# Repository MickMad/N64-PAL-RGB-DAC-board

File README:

N64 PAL RGB DAC board

Created by Michele Perla

The tile says it all. The hackaday project page says it even better :)

Inspired by Tim Worthington's PAL RGB mod : http://members.optusnet.com.au/eviltim/n64rgb/n64rgb.html

Hackaday.io project page : https://hackaday.io/project/4098-n64-pal-rgb-dac-board

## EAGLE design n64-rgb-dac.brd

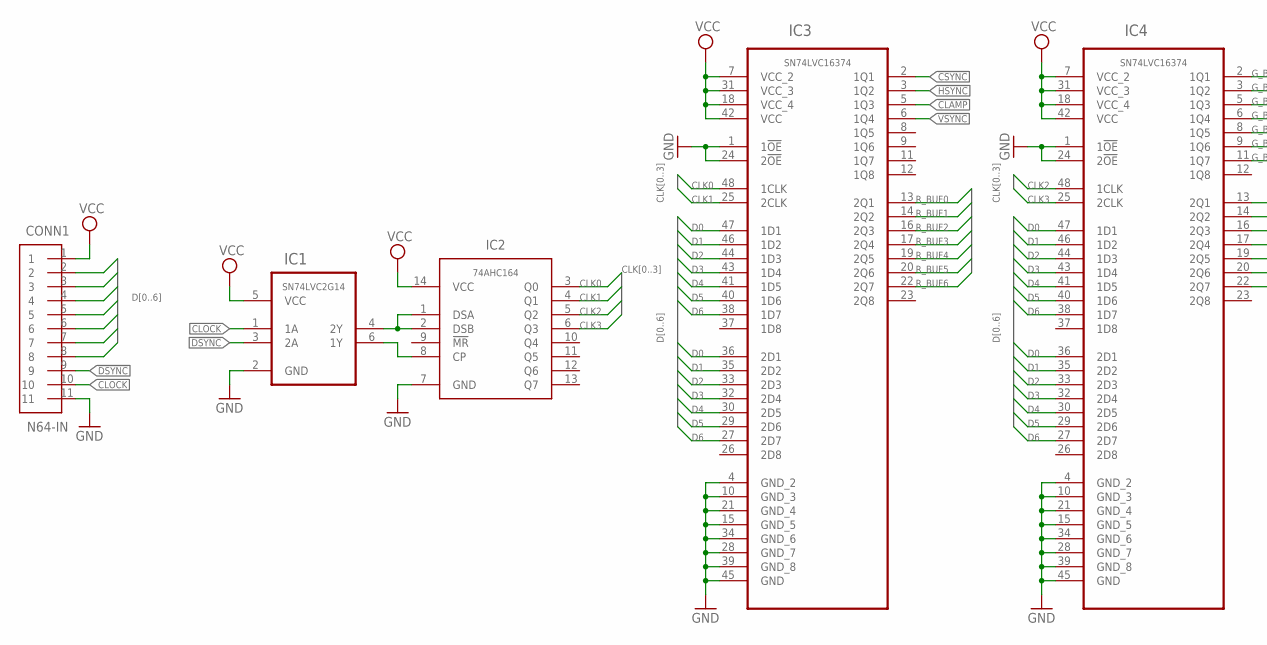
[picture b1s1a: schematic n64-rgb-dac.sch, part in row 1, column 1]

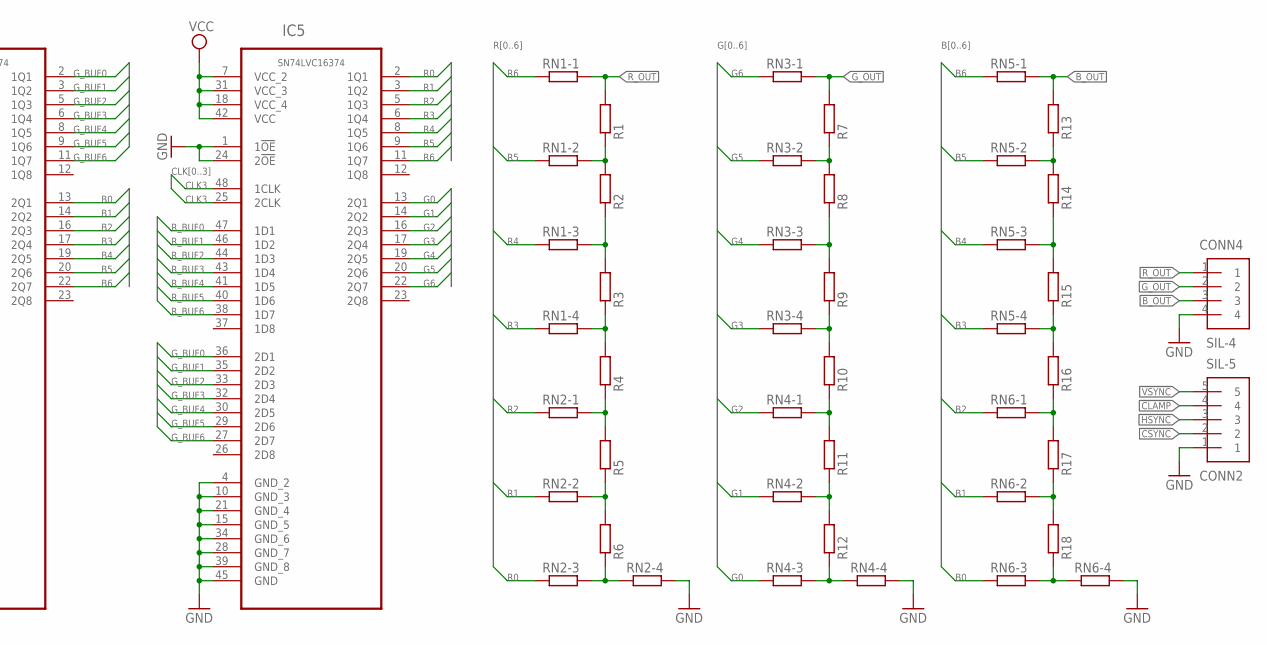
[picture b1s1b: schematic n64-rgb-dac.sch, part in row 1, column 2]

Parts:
CONN1: N64-IN; SIL-SMD-11
CONN2: SIL-5; SIL-SMD-5
CONN4: SIL-4; SIL-SMD-4
IC1: SN74LVC2G14; SOT65P210X110-6N
IC2: 74AHC164PW; SOT402-1
IC3, IC4, IC5: SN74LVC16374DL; SOP63P1035X279-48N
R1, R2, R3, R4, R5, R6, R7, R8, R9, R10, R11, R12, R13, R14, R15, R16, R17, R18: R-EU_R0603; R0603
RN1, RN2, RN3, RN4, RN5, RN6: TC164; R0603_NET_4

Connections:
!CLAMP: CONN2.4, IC3.5 (1Q3)
!CSYNC: CONN2.2, IC3.2 (1Q1)
!DSYNC: CONN1.9, IC1.3 (2A)
!HSYNC: CONN2.3, IC3.3 (1Q2)
!VSYNC: CONN2.5, IC3.6 (1Q4)
B0: IC4.13 (2Q1), RN6.5 (1)
B1: IC4.14 (2Q2), RN6.3 (1)
B2: IC4.16 (2Q3), RN6.1
B3: IC4.17 (2Q4), RN5.7 (1)
B4: IC4.19 (2Q5), RN5.5 (1)
B5: IC4.20 (2Q6), RN5.3 (1)
B6: IC4.22 (2Q7), RN5.1
B_OUT: CONN4.3, R13.2, RN5.2
CLK0: IC2.3 (Q0), IC3.48 (1CLK)
CLK1: IC2.4 (Q1), IC3.25 (2CLK)
CLK2: IC2.5 (Q2), IC4.48 (1CLK)
CLK3: IC2.6 (Q3), IC4.25 (2CLK), IC5.25 (2CLK), IC5.48 (1CLK)
CLOCK: CONN1.10, IC1.1 (1A)
D0: CONN1.2, IC3.36 (2D1), IC3.47 (1D1), IC4.36 (2D1), IC4.47 (1D1)
D1: CONN1.3, IC3.35 (2D2), IC3.46 (1D2), IC4.35 (2D2), IC4.46 (1D2)
D2: CONN1.4, IC3.33 (2D3), IC3.44 (1D3), IC4.33 (2D3), IC4.44 (1D3)
D3: CONN1.5, IC3.32 (2D4), IC3.43 (1D4), IC4.32 (2D4), IC4.43 (1D4)
D4: CONN1.6, IC3.30 (2D5), IC3.41 (1D5), IC4.30 (2D5), IC4.41 (1D5)
D5: CONN1.7, IC3.29 (2D6), IC3.40 (1D6), IC4.29 (2D6), IC4.40 (1D6)
D6: CONN1.8, IC3.27 (2D7), IC3.38 (1D7), IC4.27 (2D7), IC4.38 (1D7)
G0: IC5.13 (2Q1), RN4.5 (1)
G1: IC5.14 (2Q2), RN4.3 (1)
G2: IC5.16 (2Q3), RN4.1
G3: IC5.17 (2Q4), RN3.7 (1)
G4: IC5.19 (2Q5), RN3.5 (1)
G5: IC5.20 (2Q6), RN3.3 (1)
G6: IC5.22 (2Q7), RN3.1
GND: CONN1.11, CONN2.1, CONN4.4, IC1.2 (GND), IC2.7 (GND), IC3.1 (1!OE), IC3.4 (GND_2), IC3.10 (GND_3), IC3.15 (GND_5), IC3.21 (GND_4), IC3.24 (2!OE), IC3.28 (GND_7), IC3.34 (GND_6), IC3.39 (GND_8), IC3.45 (GND), IC4.1 (1!OE), IC4.4 (GND_2), IC4.10 (GND_3), IC4.15 (GND_5), IC4.21 (GND_4), IC4.24 (2!OE), IC4.28 (GND_7), IC4.34 (GND_6), IC4.39 (GND_8), IC4.45 (GND), IC5.1 (1!OE), IC5.4 (GND_2), IC5.10 (GND_3), IC5.15 (GND_5), IC5.21 (GND_4), IC5.24 (2!OE), IC5.28 (GND_7), IC5.34 (GND_6), IC5.39 (GND_8), IC5.45 (GND), RN2.8 (2), RN4.8 (2), RN6.8 (2)
G_BUF0: IC4.2 (1Q1), IC5.36 (2D1)
G_BUF1: IC4.3 (1Q2), IC5.35 (2D2)
G_BUF2: IC4.5 (1Q3), IC5.33 (2D3)
G_BUF3: IC4.6 (1Q4), IC5.32 (2D4)
G_BUF4: IC4.8 (1Q5), IC5.30 (2D5)
G_BUF5: IC4.9 (1Q6), IC5.29 (2D6)
G_BUF6: IC4.11 (1Q7), IC5.27 (2D7)
G_OUT: CONN4.2, R7.2, RN3.2
unnamed: IC1.4 (2Y), IC2.1 (DSA), IC2.2 (DSB)
unnamed: IC1.6 (1Y), IC2.8 (CP)
unnamed: R1.1, R2.2, RN1.4 (2)
unnamed: R2.1, R3.2, RN1.6 (2)
unnamed: R3.1, R4.2, RN1.8 (2)
unnamed: R6.1, RN2.6 (2), RN2.7 (1)
unnamed: R7.1, R8.2, RN3.4 (2)
unnamed: R5.1, R6.2, RN2.4 (2)
unnamed: R4.1, R5.2, RN2.2
unnamed: R8.1, R9.2, RN3.6 (2)
unnamed: R9.1, R10.2, RN3.8 (2)
unnamed: R12.1, RN4.6 (2), RN4.7 (1)
unnamed: R11.1, R12.2, RN4.4 (2)
unnamed: R10.1, R11.2, RN4.2
unnamed: R13.1, R14.2, RN5.4 (2)
unnamed: R14.1, R15.2, RN5.6 (2)
unnamed: R15.1, R16.2, RN5.8 (2)
unnamed: R18.1, RN6.6 (2), RN6.7 (1)
unnamed: R17.1, R18.2, RN6.4 (2)
unnamed: R16.1, R17.2, RN6.2
R0: IC5.2 (1Q1), RN2.5 (1)
R1: IC5.3 (1Q2), RN2.3 (1)
R2: IC5.5 (1Q3), RN2.1
R3: IC5.6 (1Q4), RN1.7 (1)
R4: IC5.8 (1Q5), RN1.5 (1)
R5: IC5.9 (1Q6), RN1.3 (1)
R6: IC5.11 (1Q7), RN1.1
R_BUF0: IC3.13 (2Q1), IC5.47 (1D1)
R_BUF1: IC3.14 (2Q2), IC5.46 (1D2)
R_BUF2: IC3.16 (2Q3), IC5.44 (1D3)
R_BUF3: IC3.17 (2Q4), IC5.43 (1D4)
R_BUF4: IC3.19 (2Q5), IC5.41 (1D5)
R_BUF5: IC3.20 (2Q6), IC5.40 (1D6)
R_BUF6: IC3.22 (2Q7), IC5.38 (1D7)
R_OUT: CONN4.1, R1.2, RN1.2
VCC: CONN1.1, IC1.5 (VCC), IC2.14 (VCC), IC3.7 (VCC_2), IC3.18 (VCC_4), IC3.31 (VCC_3), IC3.42 (VCC), IC4.7 (VCC_2), IC4.18 (VCC_4), IC4.31 (VCC_3), IC4.42 (VCC), IC5.7 (VCC_2), IC5.18 (VCC_4), IC5.31 (VCC_3), IC5.42 (VCC)

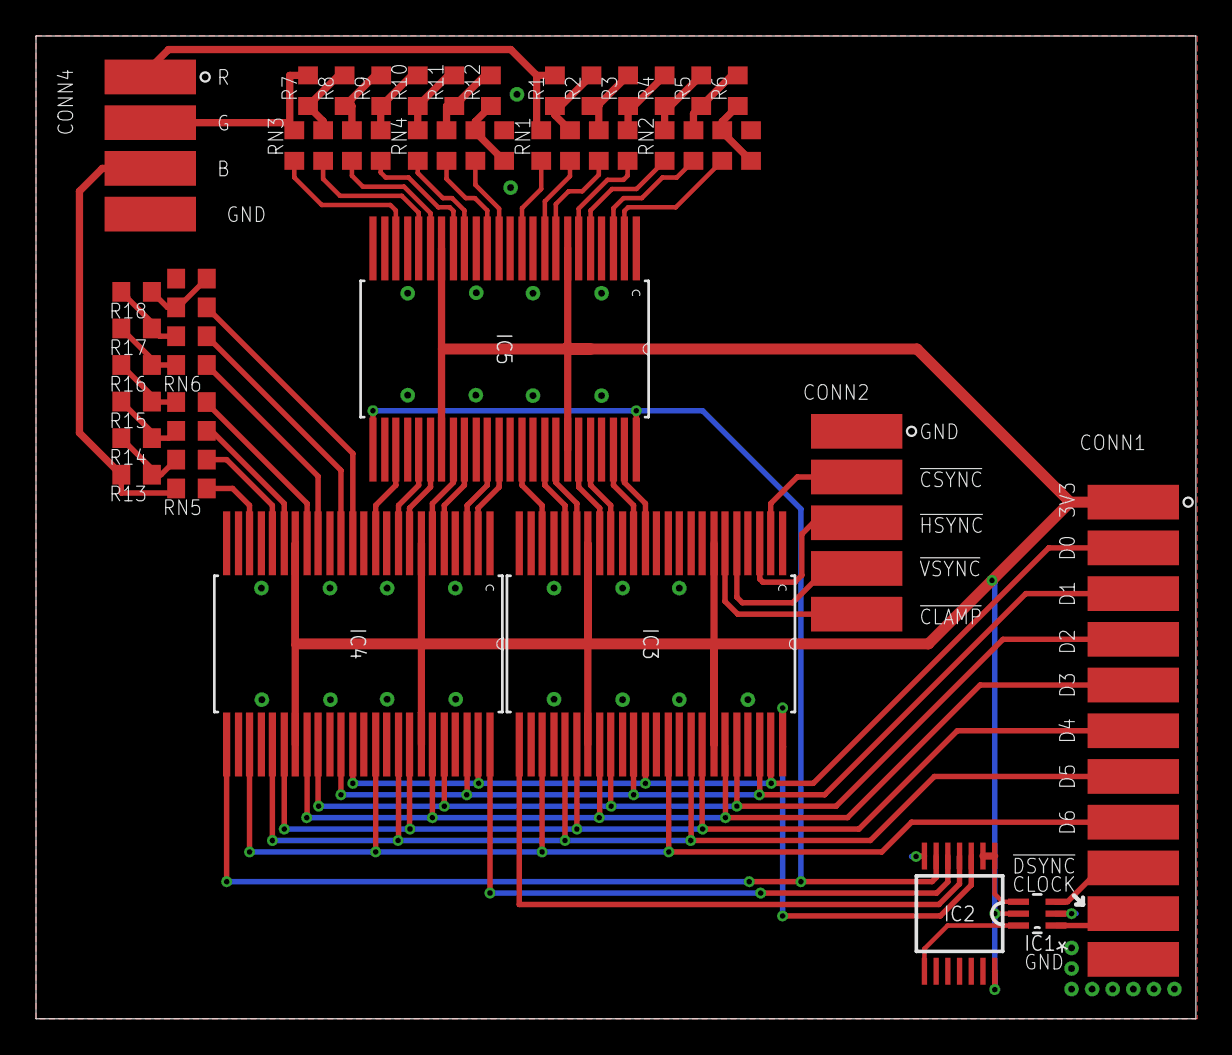
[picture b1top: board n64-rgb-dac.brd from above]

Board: 2 copper layers, 64.4 x 54.6 mm, 32 parts (0 on the bottom side), 77 nets.

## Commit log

2015-04-10 :confetti_ball: Added .gitattributes
2015-04-10 first commit
    first commit pushing rev.0 project files
